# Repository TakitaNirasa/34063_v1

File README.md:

# Eagle project 34063
includes brd and sch files.
Board has step-up and step-down config with or without transistor.

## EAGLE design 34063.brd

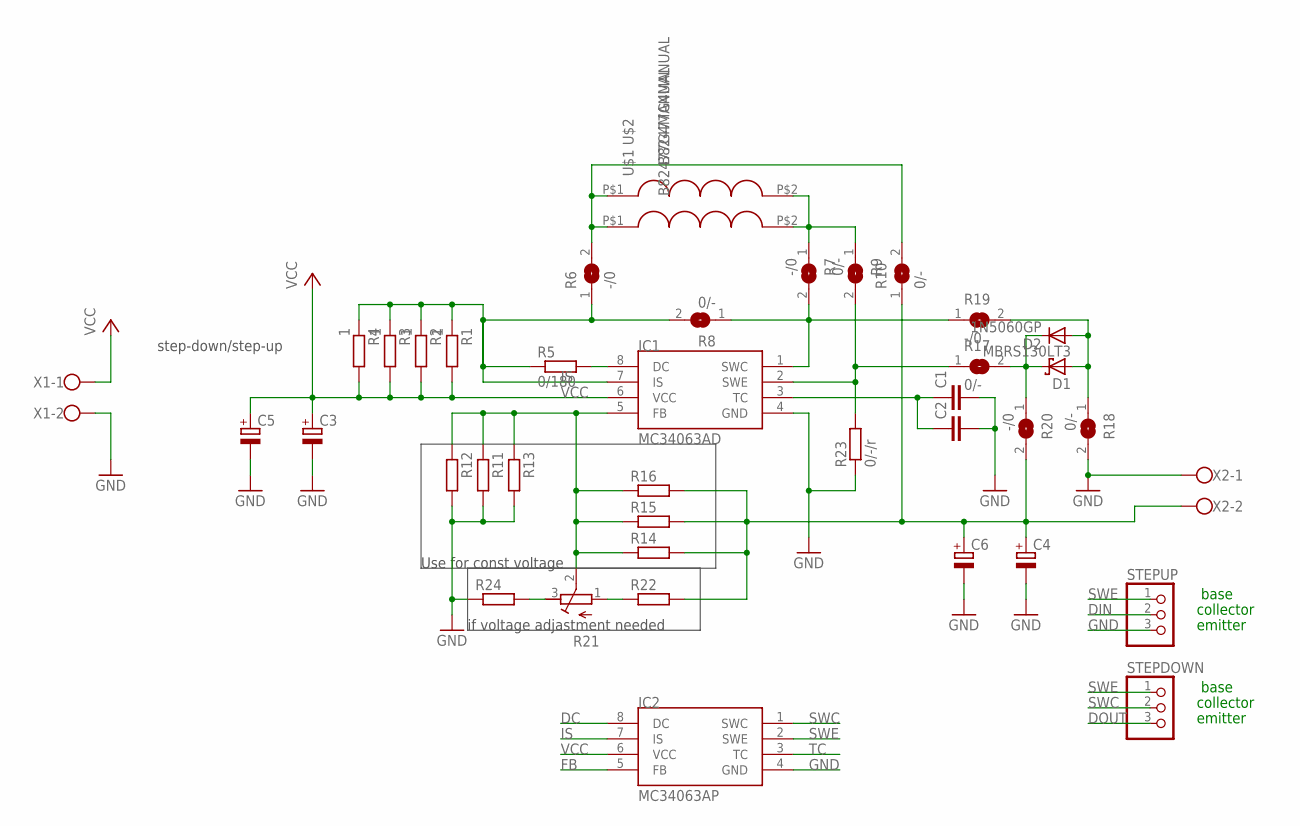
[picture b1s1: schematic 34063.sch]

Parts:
C1: C-EUC0805; C0805
C2: C-EU050-024X044; C050-024X044
C3, C4: CPOL-EUE5-13; E5-13
C5, C6: CPOL-EUE2.5-7; E2,5-7
D1: MBRS130LT3; SMB
D2: 1N5060GP; DO15-12
IC1: MC34063AD; SOIC8
IC2: MC34063AP; DIL08
R1, R2, R3, R4: 1; M1206
R5: 0/180; M0805
R6, R7, R19, R20: -/0; SJ
R8, R9, R10, R17, R18: 0/-; SJ
R11, R12, R14, R15, R22, R24: R-EU_R0805; R0805
R13, R16: R-EU_0204/2V; 0204V
R21: R-TRIMM64W; RTRIM64W
R23: 0/-/r; R0805
STEPDOWN: PINHD-1X3; 1X03
STEPUP: PINHD-1X3; 1X03
U$1, U$2: B82477G4MANUAL; B82477G4_MANUAL
X1, X2: W237-102

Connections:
DC: IC1.8 (DC), IC2.8 (DC), R5.2
DIN: D1.A, D2.A, R18.1, R19.2, STEPUP.2
DOUT: D1.C, D2.C, R17.2, R20.1, STEPDOWN.3
FB: IC1.5 (FB), IC2.5 (FB), R11.1, R12.1, R13.1, R14.1, R15.1, R16.1, R21.2 (S)
GND: C1.2, C2.2, C3.-, C4.-, C5.-, C6.-, IC1.4 (GND), IC2.4 (GND), R11.2, R12.2, R13.2, R18.2, R23.1, R24.1, STEPUP.3, X1.2, X2.1
IS: IC1.7 (IS), IC2.7 (IS), R1.1, R2.1, R3.1, R4.1, R5.1, R6.1, R8.2
L1: R7.1, R9.1, U$1.P$2, U$2.P$2
L2: R6.2, R10.2, U$1.P$1, U$2.P$1
unnamed: R21.3 (E), R24.2
unnamed: R21.1 (A), R22.1
SWC: IC1.1 (SWC), IC2.1 (SWC), R7.2, R8.1, R19.1, STEPDOWN.2
SWE: IC1.2 (SWE), IC2.2 (SWE), R9.2, R17.1, R23.2, STEPDOWN.1, STEPUP.1
TC: C1.1, C2.1, IC1.3 (TC), IC2.3 (TC)
VCC: C3.+, C5.+, IC1.6 (VCC), IC2.6 (VCC), R1.2, R2.2, R3.2, R4.2, X1.1
VOUT: C4.+, C6.+, R10.1, R14.2, R15.2, R16.2, R20.2, R22.2, X2.2

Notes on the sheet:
step-down/step-up
Use for const voltage
if voltage adjastment needed
base
collector
emitter

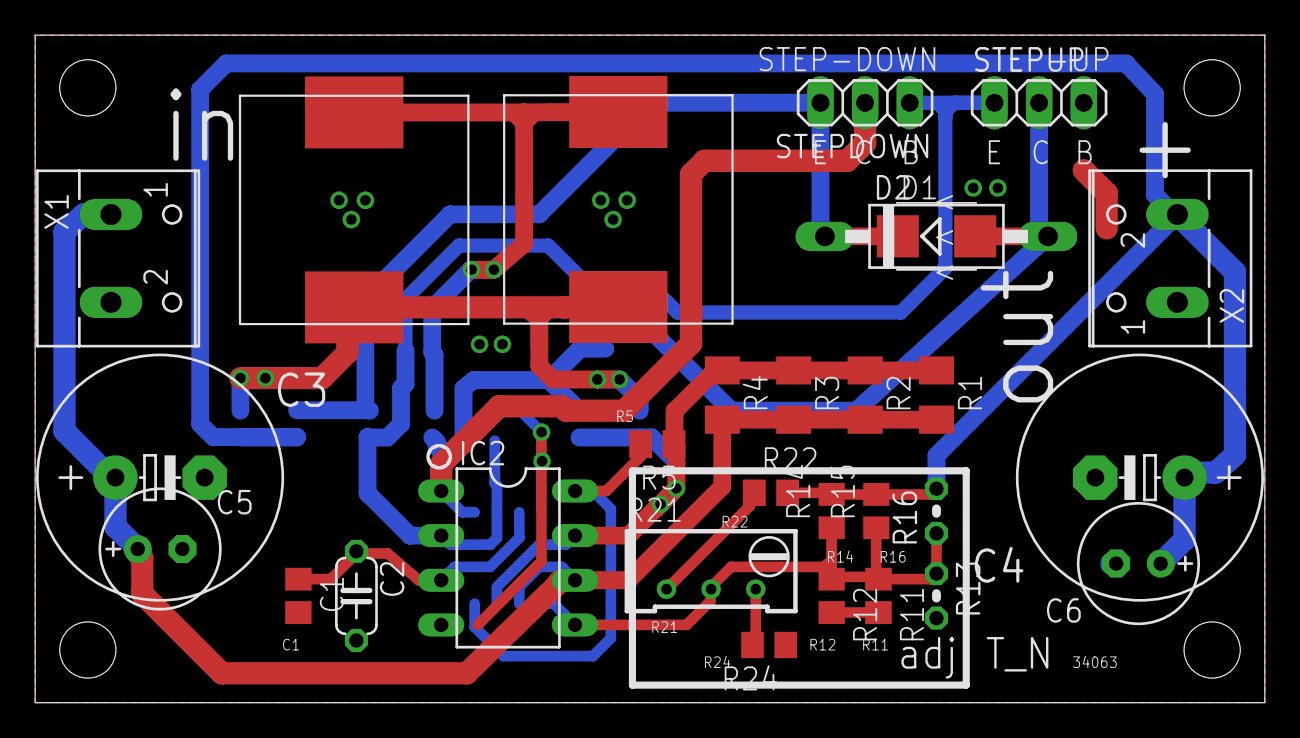
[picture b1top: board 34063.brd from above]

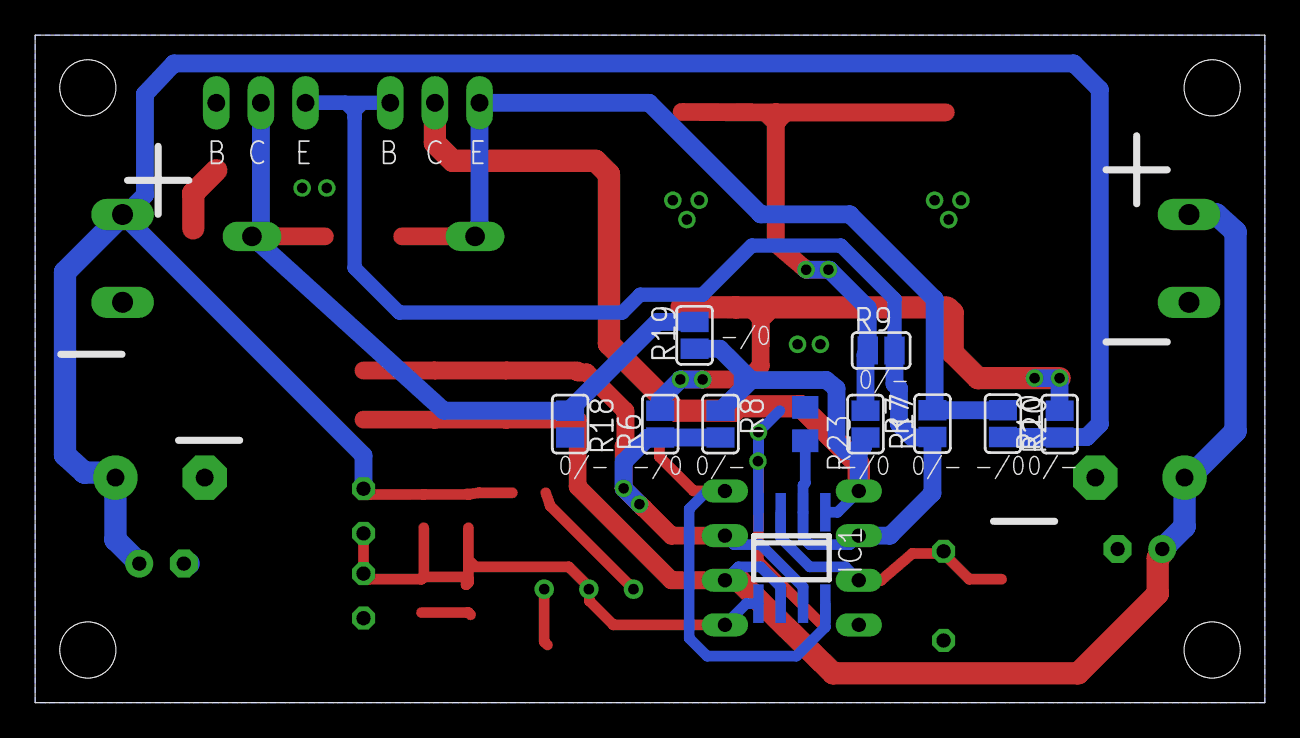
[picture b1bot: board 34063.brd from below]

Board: 2 copper layers, 70.0 x 38.0 mm, 40 parts (11 on the bottom side), 15 nets.

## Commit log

2019-10-26 add gerbers(drc pcbway passed)
2019-10-26 new image
